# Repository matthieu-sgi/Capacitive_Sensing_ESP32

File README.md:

# ESP32 capacitive sensing project for [Musical Plant Interface](https://dvic.devinci.fr/projects/plant-based-interface)

This project is a proof of concept for a capacitive sensing interface for musical instruments. It is based on the [ESP32](https://www.espressif.com/en/products/socs/esp32) microcontroller. The ESP32 is a low-cost microcontroller with integrated WiFi and Bluetooth. It is a great platform for IoT projects.

The esp32 generate a web server to simplify the calibration. It will embed a SD card to store the calibration data.

The PCB can be found in [this repository](https://github.com/matthieu-sgi/NE555_Musical_Plant_Interface) or in `PCB/NE555_Musical_Plant_Interface` folder.

## How to use

The user guide instructions are given following the picture above. 

Plug the jack from the plant electrodes in the jack on the bottom right.

Plug the jack to the speaker int the middle left jack.

Plug the DC jack in the DC jack on the middle-top right.

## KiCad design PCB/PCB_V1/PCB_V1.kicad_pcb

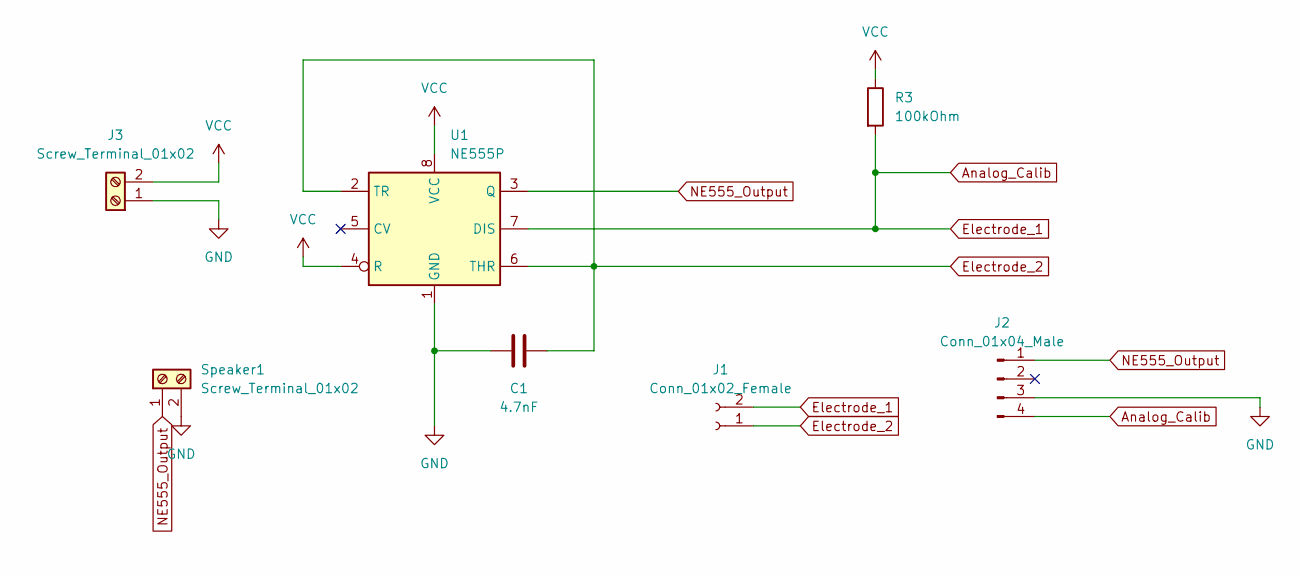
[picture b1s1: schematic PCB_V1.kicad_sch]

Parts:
C1: 4.7nF; CP_Axial_L10.0mm_D4.5mm_P15.00mm_Horizontal
J1: Conn_01x02_Female; PinSocket_1x02_P2.54mm_Vertical
J2: Conn_01x04_Male; PinSocket_1x04_P2.54mm_Vertical
J3: Screw_Terminal_01x02; TerminalBlock_bornier-2_P5.08mm
R3: 100kOhm; R_Axial_DIN0207_L6.3mm_D2.5mm_P10.16mm_Horizontal
Speaker1: Screw_Terminal_01x02; TerminalBlock_bornier-2_P5.08mm
U1: NE555P; DIP794W45P254L959H508Q8

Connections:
Analog_Calib: J1.2, J2.4, R3.2, U1.7 (DIS)
Electrode_2: C1.2, J1.1, U1.2 (TR), U1.6 (THR)
GND: C1.1, J2.3, J3.1, Speaker1.2, U1.1 (GND)
NE555_Output: J2.1, Speaker1.1, U1.3 (Q)
VCC: J3.2, R3.1, U1.4 (R), U1.8 (VCC)

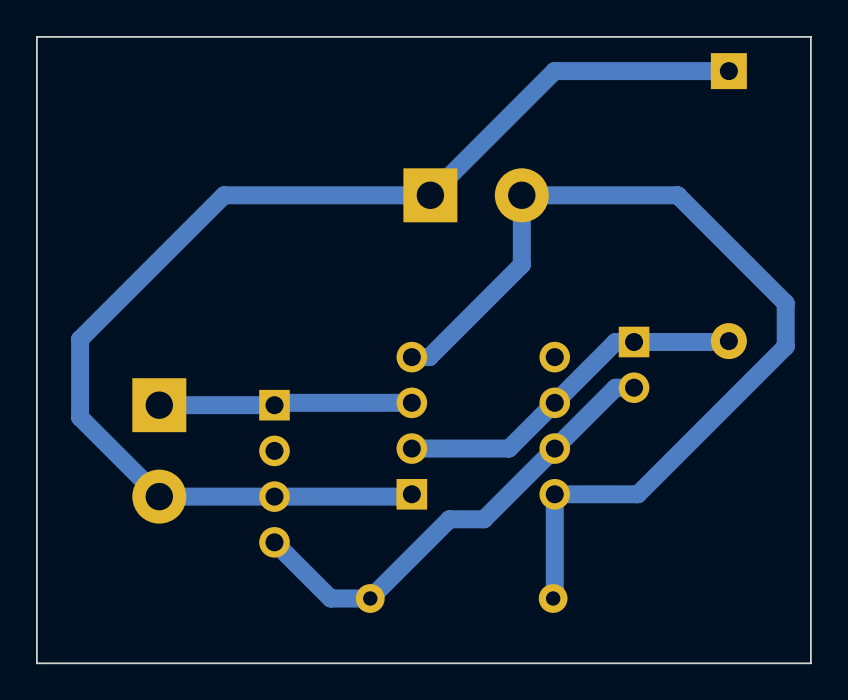
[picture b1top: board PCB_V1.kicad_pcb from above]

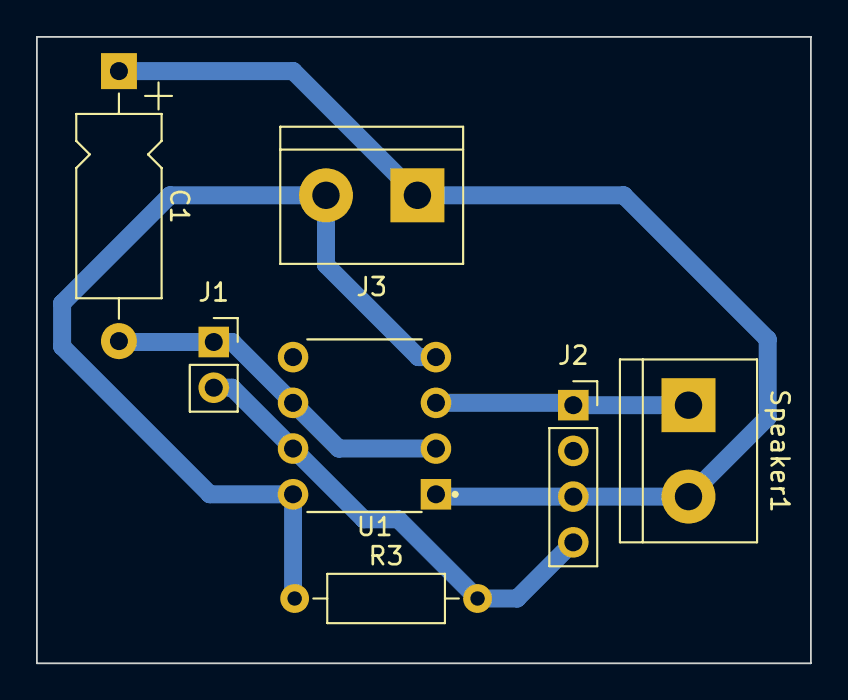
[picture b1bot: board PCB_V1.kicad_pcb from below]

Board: 2 copper layers, 43.0 x 34.8 mm, 7 parts (7 on the bottom side), 5 nets.

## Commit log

2022-11-29 add README
2022-11-29 READ
2022-11-29 Web Server created
2022-11-29 Creating website
2022-11-29 Creating old folder
2022-11-29 Webpage not displaying
2022-12-01 Adding AsyncWebserver
2022-12-02 Trying asynch web
2022-12-07 README MODIF
2023-01-23 Testing with External DAC + PCB
2023-03-29 YEEPPO
2023-03-29 adding pcb
2023-03-29 Adding PCB and readme
